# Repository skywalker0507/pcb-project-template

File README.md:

# AI PCB project template

A reproducible, audit-first PCB workflow for Codex. Reviewed atopile source is
the electrical authority, KiCad is the physical authority and independent
validator, and KiCadRoutingTools (KRT) creates isolated routing candidates.

> **Personal open-source project.** This repository also contains an ESP32-S3
> remote flashing probe design used during development, so it is not an empty
> example board. The workflow is mainly developed for Windows/WSL, Python 3.14,
> KiCad 10, and atopile. Please review and adapt design rules, parts and DRC
> results before manufacturing your own board.
>
> Project-authored code: [MIT](LICENSE). Upstream tools, CAD symbols, footprints
> and vendor models retain their own terms; see [third-party notes](docs/THIRD_PARTY.md).

The only default production path is:

```text
requirements -> electrical -> physical -> routing -> release
```

Electrical freeze is the immutable output of `electrical`, not a separate work
stage. Part selection is completed during `requirements`. Optional EDA,
alternate-router, experimental-backend and text-delegation integrations remain
available through the internal entrypoint registry, but do not enter normal
session context.

## Start a session

When this checkout hosts work on another PCB project, set the ignored
`.pcb-workspace.local.json` to `{"schema":1,"active_project":"../my-board"}`.
Session boot and `pcbctl` then use that project. Override with
`pcbctl.py --project PATH <command>`; use `--local` for this template's checks.
An invalid selection fails explicitly instead of falling back to the example.

Run existing project checks through `pcbctl.py verify project --plan`, then
`pcbctl.py verify project`. Checks with unchanged input and output hashes are
reused, including failures; no new checkpoint script is needed. See
[project check declarations and scope](docs/PROJECT_CHECKS.md).

Use Python 3.14 throughout this project:

```powershell
py -3.14 scripts/session_boot.py
```

The command writes `build/WORKSET.json` and emits one compact navigation
receipt. Read only the workset by default. Open a path from `read_if_needed`
only when the active action or a failure requires it. Never load a complete
`.kicad_pcb`, `.kicad_sch`, DSN or SES into model context.
Worksets keep bounded list previews with counts and truncation flags. In the
requirements stage, draft status and blocking unknowns are review blockers even
when the basic input structure passes; status does not replace the full gate.
Electrical contract validation and the freeze entrypoint independently apply the
same reviewed-requirements predicate. See [requirement evidence gates](docs/REQUIREMENT_GATES.md)
for cumulative scopes and explicit prototype test plans. A `reviewed` label or old passing receipt
cannot hide blocking unknowns or missing requirement structure. Freeze rechecks
the bound inputs before promotion and snapshots the requirements validator.

The Agent-facing command surface is intentionally limited to eight commands:

```powershell
py -3.14 scripts/pcbctl.py status
py -3.14 scripts/pcbctl.py build --plan
py -3.14 scripts/pcbctl.py build
py -3.14 scripts/pcbctl.py freeze
py -3.14 scripts/pcbctl.py physical-start
py -3.14 scripts/pcbctl.py place
py -3.14 scripts/pcbctl.py route
py -3.14 scripts/pcbctl.py verify
py -3.14 scripts/pcbctl.py release
```

These are thin dispatchers. Common physical and routing operations are grouped
under stable subcommands, for example `pcbctl.py place score`, `place
semantics`, `place render`, `place promote`, `route run` and `route escalate`.
An exact surviving electrical candidate blocks a duplicate build; use
`build --force-rebuild` only for an intentional compiler reproducibility check.
Build plans and successful build receipts state `validation_scope: modeled_components_only`
and include a bounded, informational snapshot of review states and declared unknowns.
This snapshot is not a completeness check or freeze authorization; live review metadata
does not change the compiler reuse fingerprint. Freeze retains its independent gates.
Advanced operations remain in `config/tool-entrypoints.json`; use them only
when no default subcommand expresses the reviewed operation.

## Create and configure a project

```powershell
py -3.14 scripts/init_project.py --new-project --project-name my-board --layers 4
py -3.14 scripts/check_pcb_environment.py --deep
py -3.14 scripts/record_toolchain_receipt.py --electrical-only
```

The initializer never installs or downloads tools. The production path expects
Git, Python 3.14, KiCad 10 and atopile. Konnect is a bounded live-KiCad helper;
it does not replace KRT and must not author the schematic or approve release.

Use `--new-project` in a separate project checkout. It archives inherited
requirements, decisions, selected parts, footprint provenance and adoption
pointers under `tmp/project-initialization/`, then creates unreviewed drafts.
Placement, routing and manufacturing inputs are reset to project drafts too;
old routing strategies, fabrication overrides and approval references are
archived. The new board path and future review paths belong to the new project.
Existing CAD and release artifacts remain on disk; a different project's freeze
cannot be adopted. Project-specific placement, routing and manufacturing inputs
still require review for the new design. Without `--new-project`, initialization
only reconfigures the current project and preserves its identity and progress.

Electrical builds audit every candidate footprint against local resources under
the configured backend `source_root`, including nested resource directories.
Pad numbering/geometry, source identity properties and footprint rule areas must
survive export before a build can pass or freeze. Compile-time library tables use
current resource paths; the existing physical board and its library table are
restored after compilation. Failed builds return a bounded cause and receipt path.
Physical-start resolves footprint libraries from the immutable freeze's source
snapshot and rejects stale physical tables before creating a candidate board.
For atopile 0.15.8's missing footprint-zone schema, the build adapter retains the
raw compiler PCB and produces a separate candidate containing the omitted source
rule areas. Recovery rejects partial/mismatched areas or other resource errors,
checks exact electrical/geometry parity, and still requires the independent
all-component integrity gate. It never repairs a routed physical board.
Cross-file consistency checks only the impedance channels explicitly declared in
`requirements.controlled_impedance` (use `{}` for a design without them). Stack
identity, target, optional exact geometry/layer sequence and calculator evidence
are compared with project data; no USB stack or trace width is built into the
validator.

Projects may declare `source_preflight` in the selected backend in
`config/electrical-backend.json`: a workspace `script` (Python), a non-empty
`inputs` list of exact workspace files, and optional `timeout_seconds` (1–60,
default 60). `build --plan`, `build --check` and builds run it before compiling
or reusing a candidate. The script receives `--output <temporary-json-path>`
and must exit zero with `{"schema":1,"success":true,"issues":[]}`. List imported
project helpers, rule manifests and reference documents explicitly; the source
tree is already hashed. The check must preserve source, backend config and all
declared inputs. Its bounded result and hashes stay in evidence; logs stay in
tmp. No preflight means no additional process. Manufacturer dimensions and
project rules belong in the project checker/data, outside generic engine code.
Freeze rejects missing or stale declared-check evidence and snapshots its input
files. `--new-project` archives and clears inherited preflight declarations;
ordinary reconfiguration preserves them. A passing check does not approve a
footprint, placement or fabrication beyond its declared scope.

Required preflight inputs must be durable workspace files and must pass Git
ignore checks; `tmp`, `build` and generated dependency directories cannot supply
them. Optional `config/source-references.json` (schema1, non-empty `files`) pins
each reference's workspace `path`, uppercase SHA-256 `sha256` and bounded `scope`.
Store reference snapshots under `references/`; preserve their origin, third-party
notices and existing review limits. Missing, altered or ignored inputs reject
before compilation. Freeze snapshots the manifest and its exact input files.
New-project initialization archives/removes the inherited manifest and preserves
the files as historical material. Default reconfiguration preserves both.

Build plans separate compiler inputs from validation inputs. `build_required`
reports whether a compiler invocation is needed; `validation_required` reports
whether the surviving output needs current gates. An unchanged source, entry,
driver, project initialization and resolved toolchain can supply its pinned raw
compiler PCB even when checks or reference paths changed. Run the suggested
`build` command to revalidate: it copies the raw result, reruns normalization,
parity and all-component integrity, binds fresh preflight/reference evidence and
retains the original receipt. A failed new gate stops there without restarting
the compiler. Schema1 receipts require a valid full input fingerprint and every
compiler dependency before they can supply this cache; incomplete proof requires
compilation. Schema2 stores separate compiler/full fingerprints. The common
driver argument protocol has an explicit version; changes to its compile
semantics must bump that version. `--force-rebuild` remains an explicit override.

## Template engine boundary

Reusable policy compilation and manufacturing gates live in the independently
versioned `template-engine/` Python package. The project owns only reviewed
inputs, board sources, evidence and artifact paths. `config/template-engine.json`
pins the engine API, version and source digest. `scripts/` currently contains
both project adapters and shared workflow code. Checkpoint evidence validation
and restoration now live in `pcb_template_engine.checkpoint`, shared by placement
checkpoints and release-review preparation. Its callers supply explicit project
and artifact roots. The path source can later be replaced by an installed engine package
without changing the PCB command surface.

Run `py -3.14 scripts/check_template_engine.py` to verify the lock. An engine
source change fails closed until its version/digest is intentionally reviewed.

Framework script updates use the existing initializer, without reconfiguring the
PCB project. Run full template checks, then preview the target:

```powershell
py -3.14 scripts/pcbctl.py --local verify template
py -3.14 scripts/init_project.py --sync-framework ../my-board --plan
py -3.14 scripts/init_project.py --sync-framework ../my-board --apply --expect-plan-sha256 <preview-digest>
```

The preview lists counts and writes the complete change plan under the source
template's `tmp/framework-update/`; it does not change the target. Apply requires
a current full-test receipt, the exact preview digest and an identical pinned
engine. It updates only managed Python scripts, with verified backups and rollback
on a failed write. `template-runtime.lock.json` records their content hashes for
the next three-way comparison; it is a software inventory, not PCB approval.
Project-local modifications, local deletions and upstream removals stop the whole
update. Extra project scripts remain untouched. Existing projects can establish
their first inventory only when every source script already matches; differences
without a previous inventory require explicit review and reconciliation first.
`--new-project` initialization records the starting script inventory automatically;
ordinary reconfiguration preserves any existing inventory.
Engine upgrades and configuration migrations remain separate reviewed changes.
Use `--validation-receipt PATH` when full checks were saved at a nondefault path.

## Authority and gates

- Requirements and reviewed `.ato` files define electrical intent.
- Physical work starts only from an immutable passing electrical freeze.
- Any connectivity, identity, part, footprint or net-name change returns to
  atopile and creates a new freeze.
- Physical-start compares critical embedded footprints and rule areas with the
  reviewed project libraries before placement begins.
- Numeric fabrication, clearance, width and impedance values require reviewed
  evidence; the Agent may not invent them.
- Router success is candidate evidence, never release approval.
- Release requires exact-board DRC, connectivity, final electrical parity,
  visual review, DFM, package checks and the compiled manufacturing registry.
- A PCBA release requires DFM evidence recorded with the reviewed finish and
  solder-mask color, with both PCB DFM and SMT DFM executed and passing.
- `pcbctl release prepare-dfm` therefore creates an isolated, non-release
  Gerber + JLC BOM + JLC CPL candidate bound to one audited board SHA. This
  breaks the SMT-DFM dependency cycle without weakening final export gates.
- Reviewed assembly entries can declare `sourcing: "customer_supplied"` with
  an exact manufacturer and MPN. Their catalog ID may be blank; all populated
  designators remain in BOM and CPL, with the sourcing route and exact identity
  included in the hash-bound BOM. Catalog entries still require a valid C-code.
  File generation does not confirm consignment acceptance, inventory or the
  factory's assembly selection; both PCB and SMT DFM gates still apply.
- `pcbctl release prepare-dfm ... --plan` validates the exact audit, reviewed
  order and native assembly coverage before any export. It creates no candidate.
  Actual export repeats the same preflight before producing Gerbers or drills.
  Readiness distinguishes a missing/stale work packet from a verified packet
  awaiting factory PCB/SMT results; the latter includes the exact upload paths.
- Release also compares reviewed critical embedded footprints with their pinned
  libraries; missing rule areas require explicit board-level compensation.
- Under-component holes whose Excellon class does not itself prove plugging or
  filling require a manufacturer/CAM confirmation before export.

Compile the shared reviewed policy before physical work when its inputs change:

```powershell
py -3.14 scripts/compile_design_policy.py
```

This also emits `manufacturing-registry.json`. Its Gerber layer-presence and
geometry rules come from `config/manufacturing-rules.json`; special-process
rules come from `config/manufacturing-profile.json`. All are bound to the same
design-policy SHA and are evaluated in `validate`, `pre_export` and `gerber`
phases. Engine code contains no component-specific manufacturing branches.
The external-DFM phase also rejects reports whose order parameters or executed
analysis modules differ from the reviewed order profile.

## Efficient physical workflow

Validation has three tiers, defined in `config/validation-tiers.json`:

- `quick`: isolated candidate integrity, DRC delta and connectivity. Render one
  cropped copper image only for critical, awkward or uncertain edits.
- `checkpoint`: full DRC/connectivity after a functional block. If footprints
  moved, rerun placement semantics and relative routability comparison. Review
  whole-board front/back copper, without 3D.
- `release`: full pipeline, exact-board placement semantics, four-view visual
  review, parity and manufacturing gates.

For a placement checkpoint, one existing command plans and runs integrity,
placement semantics, routability, electrical parity, DRC/connectivity and
front/back copper rendering:

```powershell
py -3.14 scripts/pcbctl.py verify --placement-state moved --board <candidate> `
  --baseline-board <placement-baseline> --plan
py -3.14 scripts/pcbctl.py verify --placement-state moved --board <candidate> `
  --baseline-board <placement-baseline>
```

Use `--placement-state unchanged` with the actual predecessor after copper or
silkscreen edits: native placement immutability replaces semantics/scoring.
Exact unchanged checkpoints automatically reuse hash-bound evidence without
starting another run. Board/project rules, source resources, freeze contents,
producers, policies, native tools and generated evidence must remain unchanged;
reuse is conservative for the whole batch. `--plan` creates no run or approval.
The compact result names pending visual review and critical probes. Generated
images are review inputs; this command never adopts a board, completes a stage
or approves release. Existing DRC-only checkpoint usage remains available.

For formal adoption after copper edits, `place immutability --input <reviewed-layout>
--candidate <routed-board> --inherit-checkpoint <passing-placement-summary>
--output <proof>` can reuse the original placement semantics and routability
comparison. It requires equal native footprint/pad/net/outline inputs, unchanged
metric rules and checker/runtime hashes. If only probe coverage grew, supply an
original `--reference-policy <archive>` matching the checkpoint's recorded hash;
current probe requirements still apply. Pass the proof as `--placement-inheritance`
to `place review` (with original `--placement-semantics`) and `place promote`
(with original `--routability`), then as `--placement-evidence` to physical review.
The proof tracks rule-file absence as well as content; release reviews still
require their exact-board semantics. No original receipt is rewritten.

Before the full release tier, run `pcbctl.py verify readiness --board <adopted
board>`. It aggregates cached DRC, parity, physical review, DFM and special
process status in one compact receipt. Readiness and the DRC-review writer use
`config/pcb-flow.json` → `audit.baseline`, matching the guarded release audit;
an unrelated example baseline is not project approval. Standalone audit calls
can select their baseline explicitly with `--baseline`.

Release navigation retains all open-item counts, including deferred hardware
acceptance. These notes do not become release blockers unless the reviewed gate
requires them. Review preparation/finalization close failed runs automatically.
Workflow profiling reports measured synchronous execution separately from run
lifecycle and labels legacy records without execution timing. Declaring a
mitigation implemented does not suppress an observed efficiency finding.

Aggregate placement checkpoints and release review preparation also reuse
individual native checks. Each record binds its normalized command, producer
closure, toolchain, conservative configuration/resource inventory, upstream
file contents and output hashes. Missing contracts, dynamic imports or unknown
producers disable step reuse. Supplier mappings are omitted only for audited
native producers that do not read them; electrical identity stays bound.

After a failure, repeat the same command with a new/default run ID to resume
valid steps. The existing checkpoint index distinguishes a passing `receipt`
from a `resume_receipt`; release progress uses the existing run manifest and
release-input index. Progress never approves a stage or release. Materialized
outputs retain hashes of their original proof files as well as current copies.
Final review rejects changed inputs, missing files or tampered source evidence.

`pcbctl verify prepare-review --plan` reports per-check run/reuse decisions;
`--refresh-step footprint-equivalence` recomputes just that check. `--refresh`
still recomputes the entire review packet. Full DRC/connectivity and exact-board
release placement/visual/manufacturing requirements remain in force. Workflow
metrics expose recorded executed/reused step counts; these are command counts,
not token measurements.

Native Python dependencies used by cached checks are declared in
`config/toolchain-policy.json` under `kicad.python_modules` (currently `PIL`).
Their package files and native library directories are fingerprinted; imports
without a known dependency binding disable step reuse. Artifact cleanup follows
JSON receipt references transitively, including path keys in hash maps, and
refuses to prune through malformed referenced JSON.
`pcbctl.py release` fails immediately if
that receipt is missing, stale or blocked, avoiding repeated partial pipelines.
Current exact-board evidence is selected through `build/07-release/INPUTS.json`;
the index records failed receipts too and never implies approval.
When no `--board` is supplied, release resolves the hash-checked artifact in
`build/06-routing/CURRENT.json`; it never falls back to a mutable working board.

`pcbctl.py verify prepare-review` creates the exact DRC report/audit, bounded
footprint equivalence, placement semantics and four-view bundle in one run. It
also emits an intentionally incomplete assessment template. After a reviewer
inspects all four views and saves a separate assessment, `verify finalize-review`
validates that assessment and binds the visual, exact DRC and physical-review
receipts. The generated template itself is rejected as approval.

Manufacturing/CAM confirmations use `pcbctl.py release confirm-process` with an
allowlisted outcome and a real evidence file. The command records hashes,
updates the reviewed manufacturing profile atomically and recompiles policy;
it cannot substitute for PCB/SMT DFM.

Do not run placement semantics when footprints did not move. Do not run the
full pipeline or render four views after each trace.

At functional checkpoints, or after repeated candidate rejection, run the
metadata-only workflow profiler:

```powershell
py -3.14 scripts/pcbctl.py verify workflow
```

It reads compact receipts, run timestamps and file metadata only. It never
opens PCB/image/log contents, and reports candidate churn, repeated same-board
pipeline runs, slow operation families and retention pressure. Do not run it
after every trace. A fresh hash-bound checkpoint receipt should be reused for
handoff and diagnosis while its dependencies are unchanged; release gates are
always rerun after any bound dependency changes.

For an unchanged local checkpoint, explicit reuse is available:

```powershell
py -3.14 scripts/pcbctl.py verify --tier checkpoint --board <board> `
  --baseline-board <baseline> --reuse-checkpoint <passing-pipeline-summary.json>
```

Reuse fails closed unless board/baseline SHA, every project script and JSON
policy, template-engine source and the recorded toolchain receipt are unchanged.
It is forbidden for release and electrical builds.

When changing the template implementation itself, use `pcbctl verify template`.
It captures unit-test and static-check output under
`build/00-shared/template-checks/` and prints only one compact result. This is
developer regression evidence, not a PCB checkpoint or production gate.

Placement is judged by function before appearance. `placement-semantics.json`
protects decoupling, switch-mode power loops, connector-side ESD,
receiver-side termination, antenna keepouts and connector access.
Switch-mode input capacitors are judged as a complete VIN/GND current loop,
including plane-entry vias, not by one short pad distance.
`placement-routability.json` adds relative weighted airwire length, MST length,
crossings and critical-group comparison:

```powershell
py -3.14 scripts/check_kicad_placement_routability.py `
  --baseline <old.kicad_pcb> --board <candidate.kicad_pcb> `
  --require-improvement --output <receipt.json>
```

This metric is a placement screen, not proof of routability. Before committing
the floorplan, trial-route the critical USB, power and ground-return groups.

Route critical/high-risk paths first. Batch several related low-risk nets into
one KRT candidate and audit once per functional block. A route family is bound
to its placement, obstacle-copper fingerprint, nets, profile and allowed layers.
The routing task classifier sends short, unrouted two-pad connections to a
bounded explicit trace plan and reserves KRT for actual search or useful net
batches. Reviewed functional ordering is enforced; for example, connector
configuration and data fanout must not be deferred until after a power trunk
occupies the same escape corridor. Explicit trace plans reject approximate
existing-copper conflicts before creating a candidate, but KiCad DRC remains
the exact acceptance check.

Project-specific trace scopes live in a routing profile's reviewed
`explicit_trace` block: finite `nets`, `via_nets` and matching outer `layers`.
Geometry must match the reviewed manufacturing defaults. Use stable
`--route-area` and `--strategy-class`; no project net names need engine edits.
Exact copper repairs retain independent anchor-connectivity and DRC checks.
Replacement preflight resolves the exact textual removals without writing
the input, then excludes only their unique native copper UUIDs. Missing or
ambiguous matches fail closed; retained copper and pads stay obstacles.

`physical-start plane --input <board> --output <candidate> --plan <plan>`
also supports enabled outer copper layers without changing the active board.
Outer planes require a new isolated output. Plans bind the input SHA and use
the reviewed clearance; creating/filling copper does not approve routing.
Copper previews show the native stored fills and holes, and reject unfilled
zones. A zone-fill change also expands an automatic changed-copper crop.

Long KRT runs use a persistent checkpoint instead of keeping an Agent call open:

```powershell
py -3.14 scripts/pcbctl.py route start --run-id <id> <route arguments>
py -3.14 scripts/pcbctl.py route status --run-id <id>
py -3.14 scripts/pcbctl.py route finalize --run-id <id>
```

`status` only observes the existing process. `finalize` reads its compact
receipt and never launches or revalidates the route a second time.
Route and explicit-trace commands print only acceptance, failure-family and
audit indexes; use `pcbctl route report --path <krt-report.json>` for bounded
diagnostic detail. Full geometry and logs remain on disk.

Use KRT `--dry-run` as the routing work packet. It returns classification,
batch advice, route-area health and stopping conditions without artifacts.
After three consecutive rejected candidates in one route area, diagnose the
routing hypothesis before another attempt; this does not authorize placement.

Only no-path or incomplete-connectivity results count as structural failures.
Two such failures trigger a routing/corridor escalation, not an automatic
placement change. Footprints may move only after two distinct strategies fail
and the proposed placement improves routability, passes semantics and passes
critical route probes.

Every real KRT attempt therefore names a stable physical block and structural
strategy, for example `--route-area usb_input --strategy-class fcu-only`.
Changing the routed net subset does not create a new area, and numeric tuning
alone does not count as a distinct strategy. When two independent strategies fail structurally, create the mandatory
receipt before returning to physical work:

```powershell
py -3.14 scripts/assess_routing_escalation.py `
  --scope usb_input --report <attempt-a-krt-report.json> `
  --report <attempt-b-krt-report.json> --output <escalation.json>
```

The receipt may make placement review eligible, but always records
`placement_change_authorized=false`. A routing-to-physical handoff requires
that receipt. Promotion of the resulting candidate additionally requires an
unchanged board outline, an improved routability comparison and passing probe
reports for every group in `placement-routability.json`.

`--route-bbox-mm X0 Y0 X1 Y1` may bind obstacle identity to an explicitly
reviewed local corridor. If omitted, the whole-board copper fingerprint is used
conservatively; the template never guesses a local box.

## Visual review

For a bounded local copper edit:

```powershell
py -3.14 scripts/render_kicad_visual_bundle.py --board <board> `
  --tier local --trigger critical_net_changed --layer F.Cu `
  --bbox-mm <x0> <y0> <x1> <y1>
```

The local assessment is only `accept`, `awkward` or `unsafe`. Checkpoint views
use `--tier checkpoint`; release uses `--tier release`. Visual judgment is
complementary evidence and never overrides DRC, connectivity, return-path or
manufacturing gates.

## Artifacts and retention

Each internal artifact stage has `tmp`, `evidence` and `release` lanes. Large
logs and candidate boards belong in `tmp`; compact decisions and hashes belong
in `evidence`; immutable passing outputs belong in `release`. Start discovery
at `build/STAGE_RESULTS.json`, then follow the selected stage's `CURRENT.json`;
an accepted board must never be referenced only from `tmp`.

```powershell
py -3.14 scripts/artifact_store.py inventory
py -3.14 scripts/artifact_store.py prune
py -3.14 scripts/artifact_store.py checkpoint-prune
```

Both prune commands are previews unless `--apply` is explicitly supplied.
Applied pruning creates and verifies a recoverable zip before removing the
selected run directories, and never archives a release or active reference.
Reference protection includes stage/global CURRENT pointers, release INPUTS,
DFM work-packet pointers, asynchronous routing state and manufacturing
manifests. This protection is checked before an archive is created.

## Optional capabilities

EasyEDA Pro remains useful for explicit compatibility/JLC review. FreeRouting
remains an uninstalled lab-only leftover-net comparison. Experimental electrical backends
also remain available. They are not part of
the default stage capabilities, are never electrical or physical authorities,
and cannot relax release gates.

Manufacturing cost is reviewed in two layers. The project-owned cost drivers in
`config/manufacturing-profile.json` explain every selected surcharge-risk
process and its lower-cost alternative. After uploading the package, copy the
live quote into a compact JSON observation and run `pcbctl release review-quote`;
unexpected options such as an unrequested four-wire resistance test fail before
ordering. Prices are never embedded in the template because vendor pricing is volatile.

Key paths:

- `src/`, `ato.yaml`: electrical authority;
- `elec/layout/`: authoritative KiCad physical boards after freeze;
- `config/`: reviewed policies and selected evidence;
- `scripts/`: deterministic guarded operations;
- `template-engine/`: independently versioned project-neutral engine package;
- `config/template-engine.json`: project-to-engine version and source lock;
- `config/manufacturing-rules.json`: reviewed project Gerber rule source;
- `docs/MANUFACTURING_COST_REVIEW.md`: stable cost-driver and live-quote review;
- `docs/MANUFACTURING_EXTERNAL_REVIEW.md`: one SHA-bound DFM/quote work packet,
  structured external-result import, and order-time evidence rules;
- `handoff/stages/CURRENT_STAGE.json`: stage state;
- `build/WORKSET.json`: compact current-session context;
- `build/STAGE_RESULTS.json`: one compact index of accepted stage outputs;
- `build/<stage>/CURRENT.json`: pointer to that stage's adopted immutable artifact;
- `build/*/{tmp,evidence,release}`: artifact lanes;
- `manufacturing/`: intentional release exports.

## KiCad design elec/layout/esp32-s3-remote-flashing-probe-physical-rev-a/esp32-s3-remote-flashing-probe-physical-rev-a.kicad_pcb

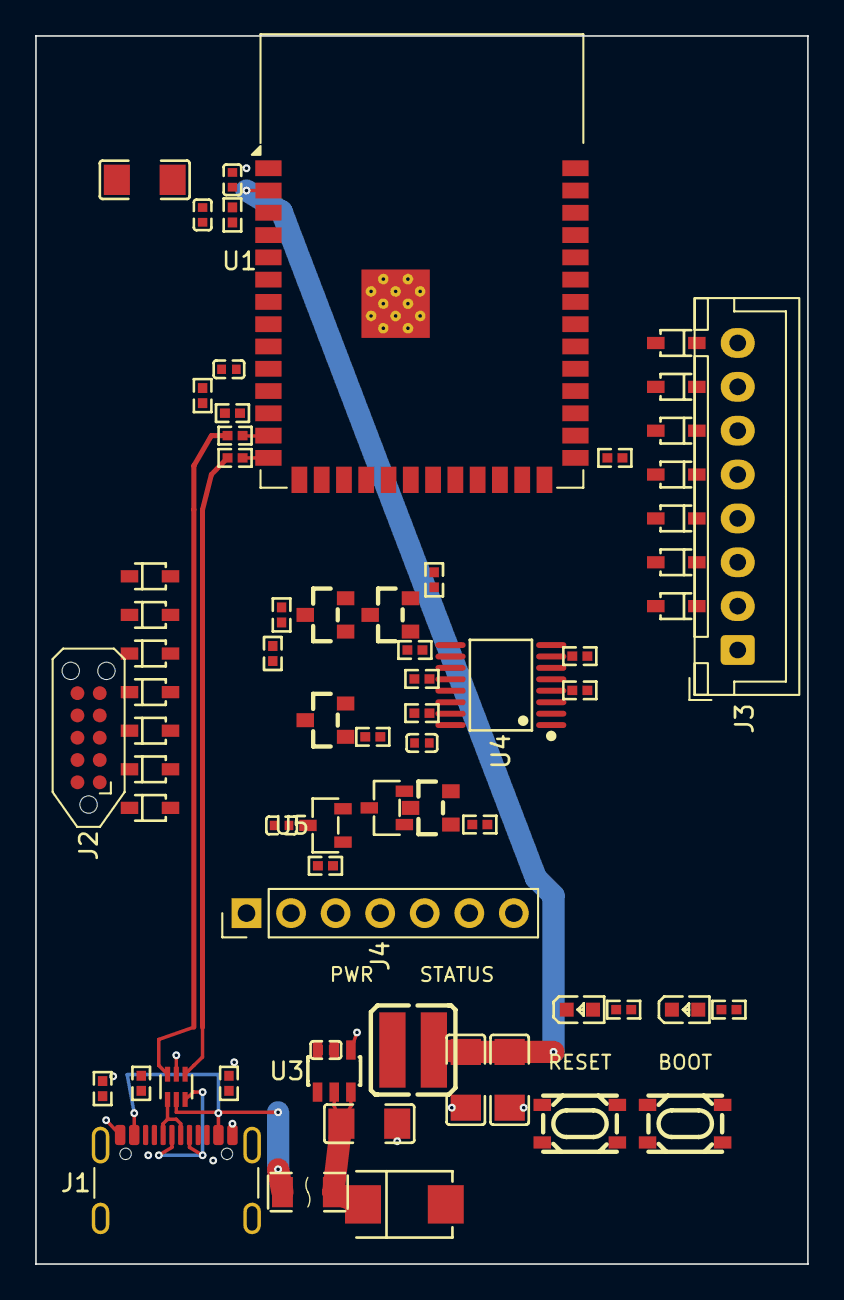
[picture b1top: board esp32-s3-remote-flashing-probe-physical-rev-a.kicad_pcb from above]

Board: 4 copper layers, 44.0 x 70.0 mm, 67 parts (0 on the bottom side), 48 nets.

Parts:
C1, C3, C5, C8, C9, C10: C0402
C2, C4, C6, C7: C1206
D1: SMB_L4.6-W3.6-LS5.3-RD
D2, D3, D4, D5, D6, D7, D8, D9, D10, D11, D12, D13, D14, D15: SOD-323_L1.8-W1.3-LS2.5-RD
F1: F1206
J1: USB_C_Receptacle_GCT_USB4105-xx-A_16P_TopMnt_Horizontal
J2: Tag-Connect_TC2050-IDC-NL_2x05_P1.27mm_Vertical
J3: JST_XH_B8B-XH-A_1x08_P2.50mm_Vertical
J4: PinHeader_1x07_P2.54mm_Vertical
L1: IND-SMD_L4.0-W4.0_XAL4040-103
LED1, LED2: LED0603-RD
Q1, Q2, Q3, Q4: SOT-23_L2.9-W1.3-P1.90-LS2.4-BR
Q5: SOT-23-3_L2.9-W1.3-P1.90-LS2.4-BR
R1, R2, R3, R4, R5, R6, R7, R8, R9, R10, R11, R12, R13, R14, R15, R16, R17, R18, R19, R20, R21, R22: R0402
SW1, SW2: SW-SMD_4P-L4.2-W3.2-P2.15-LS4.6-2
U1: ESP32-S3-WROOM-1
U2: SOT-666-6_L1.6-W1.2-P0.50-LS1.6-BR
U3: TSOT-26_L2.9-W1.6-P0.95-LS2.8-BL
U4: TSSOP-16_L5.0-W4.4-P0.65-LS6.4-BL
U5: SOT-23-3_L2.9-W1.3-P1.90-LS2.4-BR

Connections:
3V3: C1.1, C2.1, C6.1, C7.1, C8.1, J4.1, L1.2, R1.1, R7.1, R18.1, R19.1, U1.2, U3.1, U4.16
BOOT0: D8.1, D15.1, J2.7, J3.6, Q2.3, R15.1
BOOT0_ASSERT: Q3.1, R14.1, U1.7
BOOT_GATE: Q2.1, Q3.3, R13.2
BUCK_BST: C5.1, U3.6
BUCK_SW: C5.2, L1.1, U3.5
ESP_BOOT: R18.2, SW2.1, SW2.2, U1.27
ESP_EN: C3.1, R1.2, SW1.1, SW1.2, U1.3
GND: C1.2, C2.2, C3.2, C4.2, C6.2, C7.2, C8.2, C9.2, C10.2, D1.2, D2.2, D3.2, D4.2, D5.2, D6.2, D7.2, D8.2, D9.2, D10.2, D11.2, D12.2, D13.2, D14.2, D15.2, J1.A1, J1.A12, J1.B1, J1.B12, J2.3, J2.5, J2.10, J3.1, J4.2, LED1.1, LED2.1, Q1.2, Q3.2, Q5.2, R2.2, R3.2, R6.2, R12.2, R14.2, R15.2, R17.2, R21.2, SW1.3, SW1.4, SW2.3, SW2.4, U1.1, U1.40, U1.41, U2.2, U3.4, U4.1, U4.3, U4.6, U4.8, U4.10, U4.13, U5.2
GPIO10: J4.3, U1.18
GPIO11: J4.4, U1.19
GPIO12: J4.5, U1.20
GPIO13: J4.6, U1.21
GPIO14: J4.7, U1.22
NRST: D5.1, D12.1, J2.9, J3.5, Q1.3
NRST_ASSERT: Q1.1, R12.1, U1.4
POWER_LED_A: LED1.2, R19.2
PROBE_SWCLK: U1.11, U4.5
PROBE_SWDIO: U1.10, U4.2
PROBE_UART_RX: U1.9, U4.14
PROBE_UART_TX: U1.8, U4.11
STATUS_LED: R20.1, U1.23
STATUS_LED_A: LED2.2, R20.2
SWCLK: D4.1, D11.1, J2.4, J3.4, R9.2
SWCLK_MUX: R9.1, U4.7
SWDIO: D3.1, D10.1, J2.2, J3.3, R8.2
SWDIO_MUX: R8.1, U4.4
TARGET_ENABLE_REQUEST: Q4.1, R21.1, U1.17
TARGET_EN_N: Q4.3, R7.2, U4.15
TARGET_INTERLOCK: Q4.2, Q5.3
TARGET_RX: D7.1, D14.1, J2.8, J3.8, R10.2
TARGET_RX_MUX: R10.1, U4.9
TARGET_TX: D6.1, D13.1, J2.6, J3.7, R11.2
TARGET_TX_MUX: R11.1, U4.12
USB_5V: C4.1, D1.1, F1.2, U3.2, U3.3
USB_CC1: J1.A5, R2.1
USB_CC2: J1.B5, R3.1
USB_DM: R5.2, U1.13
USB_DM_ESD: R5.1, U2.3
USB_DM_RAW: J1.A7, J1.B7, U2.4
USB_DP: R4.2, U1.14
USB_DP_ESD: R4.1, U2.1
USB_DP_RAW: J1.A6, J1.B6, U2.6
USB_SHIELD: J1.SH, R6.1
USB_VBUS_RAW: F1.1, J1.A4, J1.A9, J1.B4, J1.B9, U2.5
VTREF: C10.1, D2.1, D9.1, J2.1, J3.2, Q2.2, R13.1, R16.1, R22.1, U5.3
VTREF_ADC: C9.1, R16.2, R17.1, U1.12
VTREF_OK_N: Q5.1, R22.2, U5.1

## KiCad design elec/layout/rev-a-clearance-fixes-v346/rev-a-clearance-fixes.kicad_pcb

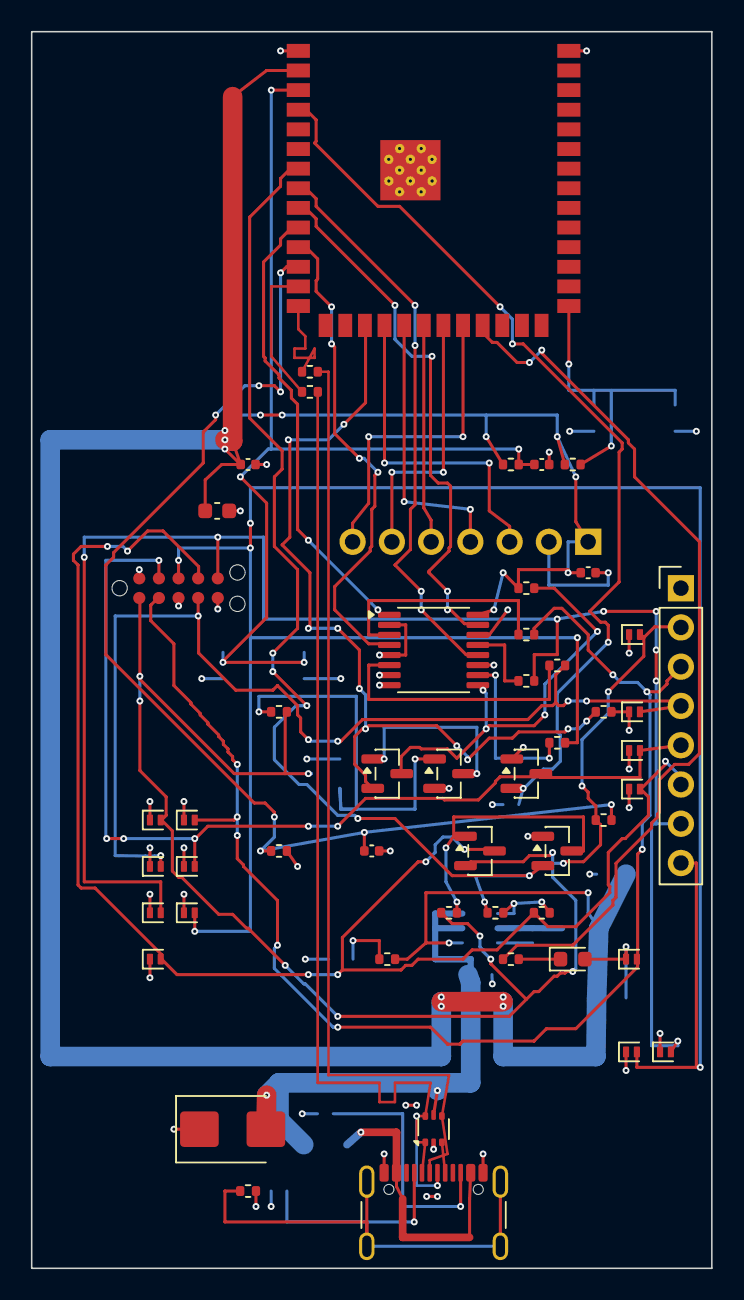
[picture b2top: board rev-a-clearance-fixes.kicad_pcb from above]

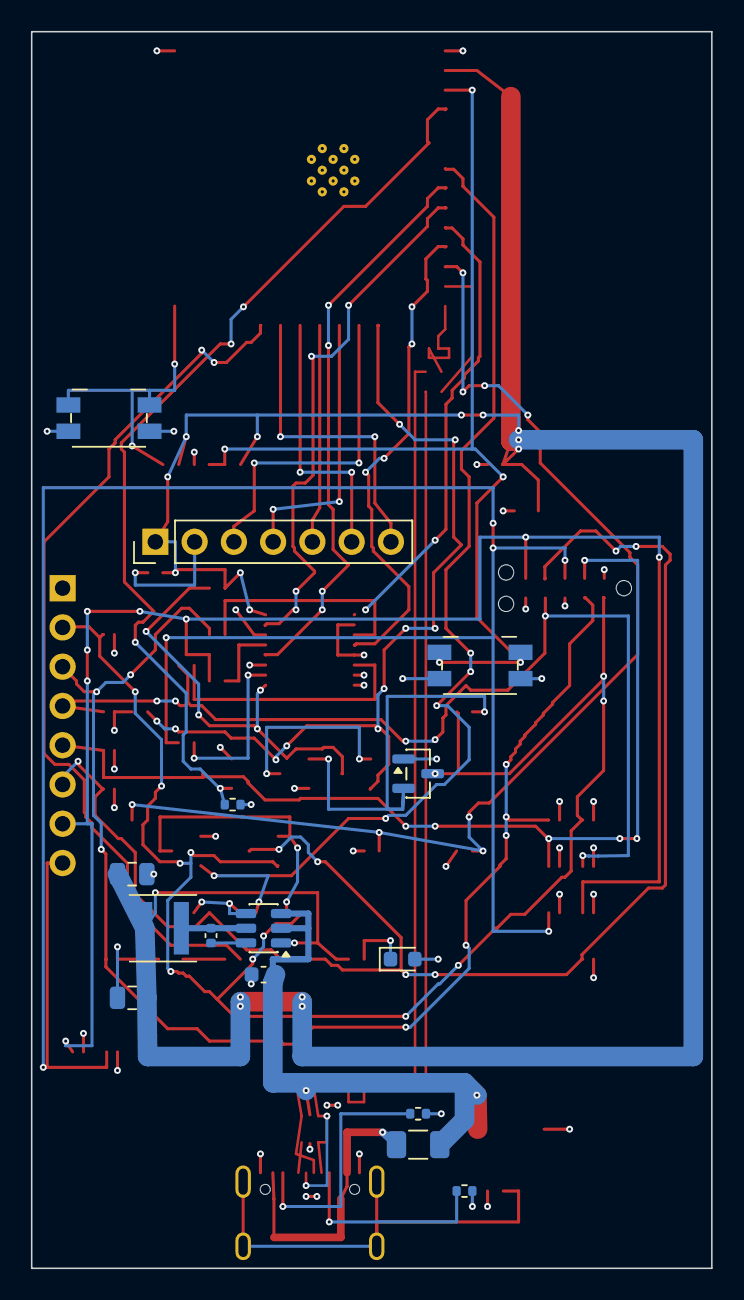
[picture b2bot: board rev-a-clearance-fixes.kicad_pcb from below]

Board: 4 copper layers, 44.0 x 80.0 mm, 66 parts (15 on the bottom side), 46 nets.

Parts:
C1, C5, C8: 100nF; C_0402_1005Metric
C2, C4: 10uF; C_0603_1608Metric
C3: 1uF; C_0402_1005Metric
C6, C7: 22uF; C_0805_2012Metric
C9: 4.7nF; C_0402_1005Metric
D1: D; D_SMB
D2, D3, D4, D5, D6, D7, D8, D9, D10, D11, D12, D13, D14, D15: PESD3V3U1UL,315; D_SOD-882
F1: 1206L075/16WR; Fuse_1206_3216Metric
J1: J1; USB_C_Receptacle_GCT_USB4105-xx-A_16P_TopMnt_Horizontal
J2: J2; Tag-Connect_TC2050-IDC-NL_2x05_P1.27mm_Vertical
J3: J3; PinHeader_1x08_P2.54mm_Vertical
J4: J4; PinHeader_1x07_P2.54mm_Vertical
L1: XGL4030-472MEC; L_Coilcraft_XxL4030
LED1, LED2: LED; LED_0603_1608Metric
Q1, Q3, Q4: 2N7002LT1G; SOT-23
Q2: AO3401A; SOT-23
Q5: AO3400A; SOT-23
R1, R7, R18: 10kΩ; R_0402_1005Metric
R2, R3: 5.1kΩ; R_0402_1005Metric
R4, R5: 22Ω; R_0402_1005Metric
R6: 0Ω; R_0402_1005Metric
R8, R9: 47Ω; R_0402_1005Metric
R10, R11, R19, R20: 1kΩ; R_0402_1005Metric
R12, R13, R14, R15, R21, R22: 100kΩ; R_0402_1005Metric
R16, R17: 1MΩ; R_0402_1005Metric
SW1, SW2: Panasonic_EVQPUJ_EVQPUA
U1: ESP32-S3-WROOM-1-N16R8; ESP32-S3-WROOM-1
U2: USBLC6-2P6; SOT-666
U3: AP63203WU-7; TSOT-23-6
U4: TMUX1574PWR; TSSOP-16_4.4x5mm_P0.65mm
U5: TLV803EA26RDBZR; SOT-23

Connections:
BOOT0: D8.2, D15.2, J2.7, J3.6, Q2.3, R15.1
BOOT0_ASSERT: Q3.2, R14.1, U1.7
BOOT0_GATE: Q2.1, Q3.3, R13.2
BUCK_BST: C5.1, U3.6
BUCK_SW: C5.2, L1.1, U3.5
CC1: J1.A5, R2.1
CC2: J1.B5, R3.1
EN: C3.1, R1.2, SW1.1, U1.3
EXP_GPIO10: J4.3, U1.18
EXP_GPIO11: J4.4, U1.19
EXP_GPIO12: J4.5, U1.20
EXP_GPIO13: J4.6, U1.21
EXP_GPIO14: J4.7, U1.22
GND: C1.2, C2.2, C3.2, C4.2, C6.2, C7.2, C8.2, C9.2, D1.1, D2.1, D3.1, D4.1, D5.1, D6.1, D7.1, D8.1, D9.1, D10.1, D11.1, D12.1, D13.1, D14.1, D15.1, J1.A1, J1.A12, J1.B1, J1.B12, J2.3, J2.5, J2.10, J3.1, J4.2, LED1.2, LED2.2, Q1.1, Q3.1, Q5.2, R2.2, R3.2, R6.2, R12.2, R14.2, R15.2, R17.2, R21.2, SW1.2, SW2.2, U1.1, U1.40, U1.41, U2.2, U3.4, U4.2, U4.5, U4.7, U4.8, U4.11, U4.14, U5.1
GPIO0: R18.2, SW2.1, U1.27
NRST: D5.2, D12.2, J2.9, J3.5, Q1.3
NRST_ASSERT: Q1.2, R12.1, U1.4
POWER_LED_A: LED1.1, R19.2
PROBE_UART_RX: U1.9, U4.15
PROBE_UART_TX: U1.8, U4.12
Q4_SOURCE: Q4.1, Q5.3
STATUS_LED: R20.1, U1.23
STATUS_LED_A: LED2.1, R20.2
SUP_RESET_N: Q5.1, R22.1, U5.2
SWCLK: D4.2, D11.2, J2.4, J3.4, R9.2
SWCLK_MUX: R9.1, U4.6
SWCLK_PROBE: U1.11, U4.4
SWDIO: D3.2, D10.2, J2.2, J3.3, R8.2
SWDIO_MUX: R8.1, U4.3
SWDIO_PROBE: U1.10, U4.1
TARGET_ENABLE_REQUEST: Q4.2, R21.1, U1.17
TARGET_EN_N: Q4.3, R7.2, U4.9
TARGET_RX: D7.2, D14.2, J2.8, J3.8, R11.2
TARGET_RX_MUX: R11.1, U4.10
TARGET_TX: D6.2, D13.2, J2.6, J3.7, R10.2
TARGET_TX_MUX: R10.1, U4.13
USB_5V: C4.1, D1.2, F1.2, U2.5, U3.2, U3.3
USB_DM: R5.2, U1.13
USB_DM_CONN: J1.A7, J1.B7, R5.1, U2.1, U2.6
USB_DP: R4.2, U1.14
USB_DP_CONN: J1.A6, J1.B6, R4.1, U2.3, U2.4
USB_SHIELD: J1.SH, R6.1
USB_VBUS_RAW: F1.1, J1.A4, J1.A9, J1.B4, J1.B9
V3V3: C1.1, C2.1, C6.1, C7.1, C8.1, J4.1, L1.2, R1.1, R7.1, R18.1, R19.1, U1.2, U3.1, U4.16
VTREF: D2.2, D9.2, J2.1, J3.2, Q2.2, R13.1, R16.1, R22.2, U5.3
VTREF_ADC: C9.1, R16.2, R17.1, U1.12

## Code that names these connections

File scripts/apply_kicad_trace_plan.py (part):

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    },
    "routing_corridor_adjustment": {
        "nets": {
            "GPIO10", "GPIO11", "GPIO12", "GPIO13", "GPIO14",
            "TARGET_EN_N", "TARGET_ENABLE_REQUEST", "VTREF_OK_N", "TARGET_INTERLOCK",
        },
        "layers": {"F.Cu", "B.Cu"},
        "via_nets": {
            "GPIO10", "GPIO11", "GPIO12", "GPIO13", "GPIO14",
            "TARGET_EN_N", "TARGET_ENABLE_REQUEST", "VTREF_OK_N", "TARGET_INTERLOCK", "GND",
        },
    },
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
